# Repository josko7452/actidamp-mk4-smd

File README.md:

# Actidamp Mk. IV - SMD

Low noise RIAA preamplifier with JFET input and active input impedance (to mitigate Johnson noise)

## Schematics

* **Main board** - [pdf link](https://github.com/josko7452/actidamp-mk4-smd/releases/download/2019.11.5/main-pcb.pdf)
* **Power supply** - [pdf link](https://github.com/josko7452/actidamp-mk4-smd/releases/download/2019.11.5/psu-brick.pdf)
* **Front & Back panel** - [pdf link](https://github.com/josko7452/actidamp-mk4-smd/releases/download/2019.11.5/panels.pdf)

## Pictures

## Getting Started

To build this just download Gerbers from release page and hand-off to your favourtie PCB manufacturer.
I have tested it with JLC PCB. But it has no crazy requirements besides the mainboard is 4 layer.

(If you want BOM, download KiCad and generate it from the Schematic, you will likely change parts anyway
dependig on accessibility.. you can shoot me a message and I will send you the Mouser part list from
my order history if you wish)

## Structure

There are 3 KiCad project for each PCB. i.e. *'main-pcb'*, *'panels'* and *'psu-brick'*.
Also there is LTSpice simulation in 'ltspice' subfolder.
Other than that it also cointains KiCad libraries used as submodules (kicad-footprints and kicad-symbols)

## Authors

* **Pavel Dudek** - *Original THT version* - [Amaterske radio 94-06](https://archive.org/stream/Amaterske_radio_1994/94-06#page/n19)
* **Bruno Kremel [me]** - *Modified to SMD and using different JFET*

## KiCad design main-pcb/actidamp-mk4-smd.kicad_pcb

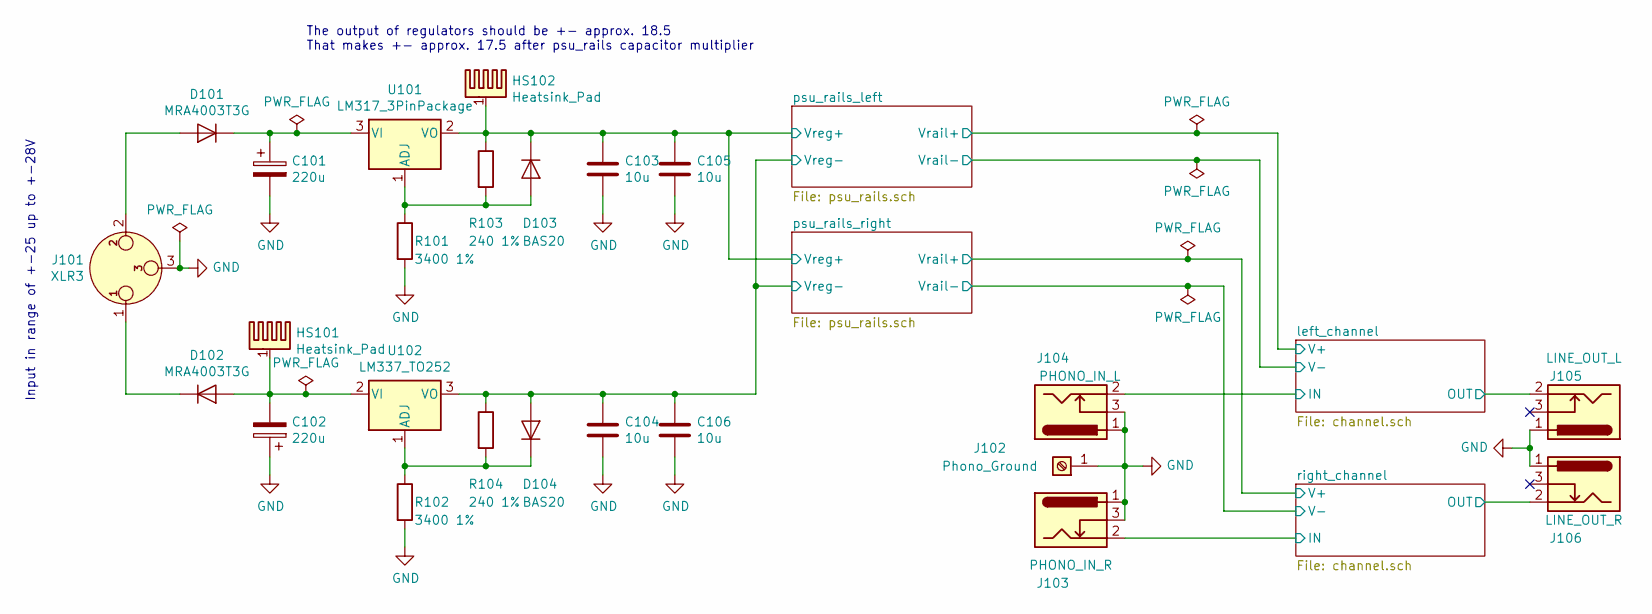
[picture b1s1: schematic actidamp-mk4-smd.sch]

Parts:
C101, C102: 220u; CP_Elec_8x10.5; Part number EEE1EA221UP
C103, C104, C105, C106: 10u; C_1206_3216Metric_Pad1.42x1.75mm_HandSolder; Part number C1206C106K3PACTU
D101, D102: MRA4003T3G; D_SMA; Part number MRA4003T3G
D103, D104: BAS20; D_SOT-23_ANK; Part number BAS20
HS101, HS102: Heatsink_Pad; Heatsink_TO252_573100; Part number FK 244 13 D PAK
J101: XLR3; MiniXLR_TRAPC3M1X; Part number TRAPC3MX
J102: Phono_Ground; SCREW_TERMINAL_SCTM4RA; Part number SCRTM4RA
J103: PHONO_IN_L; RCA_x1_PJRAN1X1U; Part number PJRAN1X1U02AUX
J104: PHONO_IN_R; RCA_x1_PJRAN1X1U; Part number PJRAN1X1U03AUX
J105: LINE_OUT_L; RCA_x1_PJRAN1X1U; Part number PJRAN1X1U02AUX
J106: LINE_OUT_R; RCA_x1_PJRAN1X1U; Part number PJRAN1X1U03AUX
R101, R102: 3400 1%; R_0603_1608Metric_Pad1.05x0.95mm_HandSolder; Part number MCWF06R3401BTL
R103, R104: 240 1%; R_0603_1608Metric_Pad1.05x0.95mm_HandSolder; Part number ERA3AEB241V
U101: LM317_3PinPackage; TO-252-3_TabPin2; Part number LM317MDTX
U102: LM337_TO252; TO-252-3_TabPin2; Part number LM337KVURG3

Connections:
/left_channel/IN: J103.2; also elsewhere on the board
/left_channel/OUT: J105.2; also elsewhere on the board
/psu_rails_left/Vreg+: C103.1, C105.1, D103.1 (K), HS102.1, R103.1, U101.2 (VO); also elsewhere on the board
/psu_rails_left/Vreg-: C104.2, C106.2, D104.2 (A), R104.1, U102.3 (VO); also elsewhere on the board
/right_channel/IN: J104.2; also elsewhere on the board
/right_channel/OUT: J106.2; also elsewhere on the board
GND: C101.2, C102.1, C103.2, C104.1, C105.2, C106.1, J101.3, J102.1, J103.1, J103.3, J104.1, J104.3, J105.1, J106.1, R101.2, R102.2; also elsewhere on the board
unnamed: C101.1, D101.1 (K), U101.3 (VI)
unnamed: C102.2, D102.2 (A), HS101.1, U102.2 (VI)
unnamed: D101.2 (A), J101.2
unnamed: D102.1 (K), J101.1
unnamed: D103.2 (A), R101.1, R103.2, U101.1 (ADJ)
unnamed: D104.1 (K), R102.1, R104.2, U102.1 (ADJ)

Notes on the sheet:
The output of regulators should be +- approx. 18.5 That makes +- approx. 17.5 after psu_rails capacitor multiplier
Input in range of +-25 up to +-28V

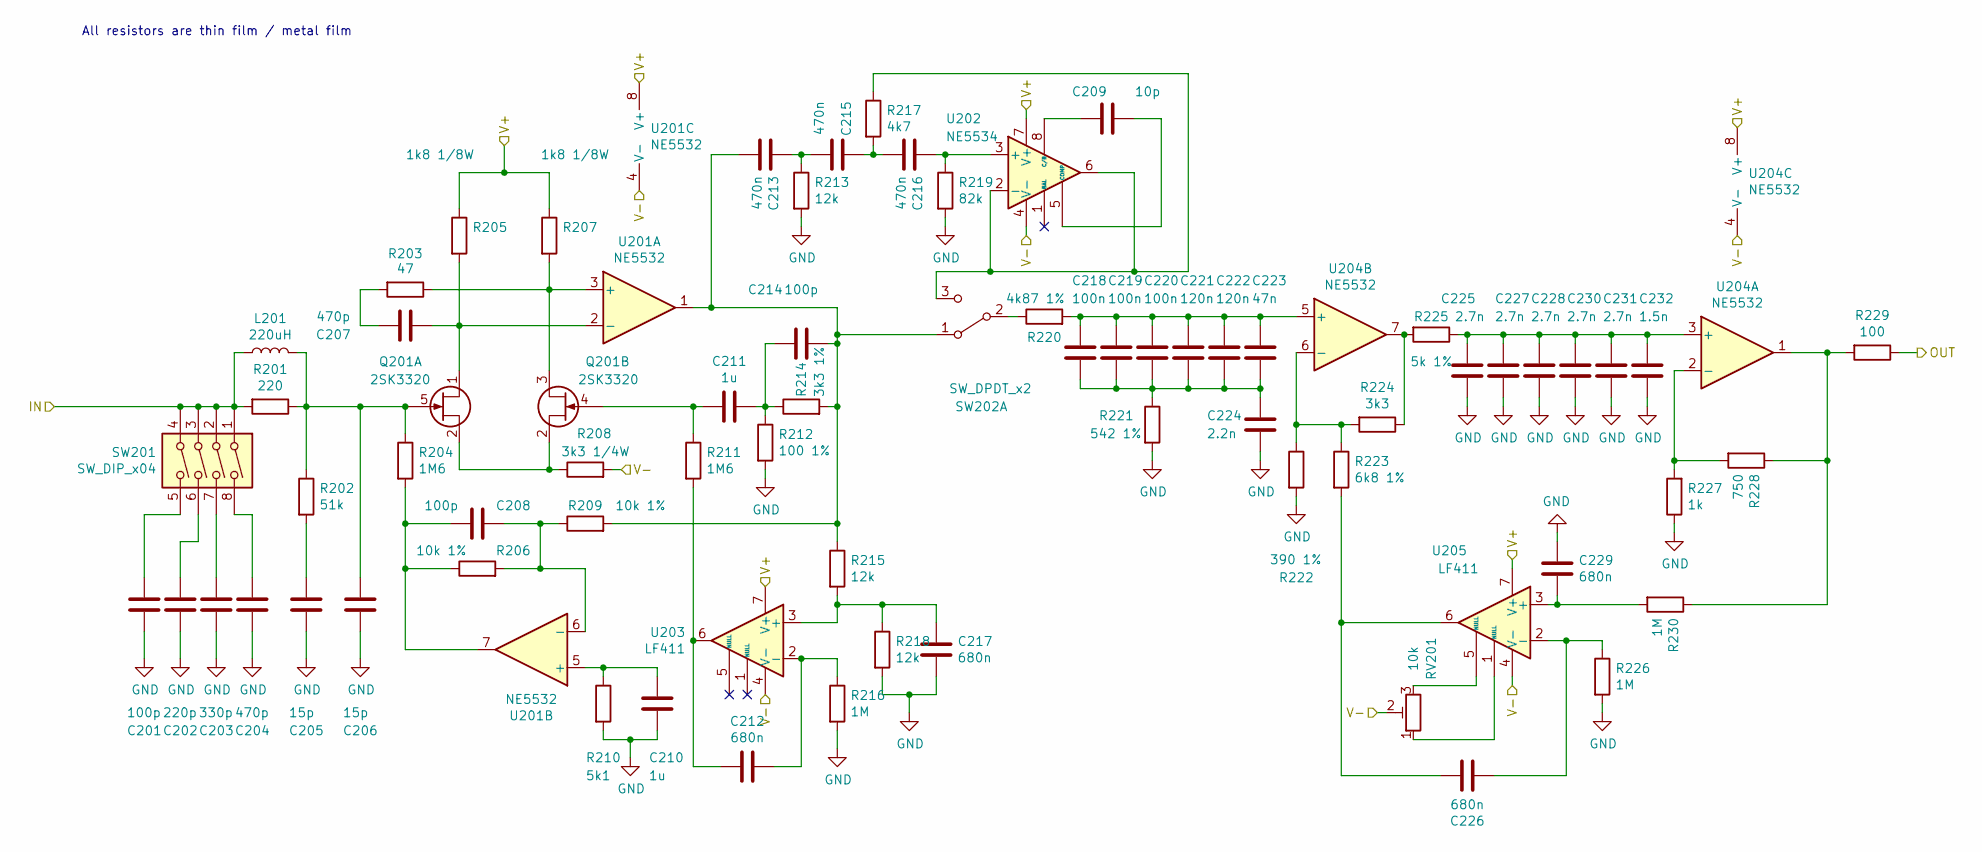
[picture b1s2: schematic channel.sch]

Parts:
C201, C208, C214: 100p; C_0603_1608Metric_Pad1.05x0.95mm_HandSolder; Part number MC0603N101J500CT
C202: 220p; C_0603_1608Metric_Pad1.05x0.95mm_HandSolder; Part number 06035A221JAT2A
C203: 330p; C_0603_1608Metric_Pad1.05x0.95mm_HandSolder; Part number MC0603N331J500CT
C204, C207: 470p; C_0603_1608Metric_Pad1.05x0.95mm_HandSolder; Part number VJ0603A471JXACW1BC
C205, C206: 15p; C_0603_1608Metric_Pad1.05x0.95mm_HandSolder; Part number MC0603N150J500CT
C209: 10p; C_0603_1608Metric_Pad1.05x0.95mm_HandSolder; Part number MC0603N100J500CT
C210, C211: 1u; C_2824_7260Metric_Pad3.20x4.45mm_HandSolder; Part number SMDIC04100TB00KQ00
C212, C217, C226, C229: 680n; C_2824_7260Metric_Pad3.20x4.45mm_HandSolder; Part number SMDIC03680TB00KQ00
C213, C215, C216: 470n; C_2824_7260Metric_Pad3.20x4.45mm_HandSolder; Part number SMDIC03470TB00MQ00
C218, C219, C220: 100n; C_1913_4833Metric_Pad1.3x3.00mm_HandSolder; Part number ECHU1H104GX9
C221, C222: 120n; C_2416_6041Metric_Pad1.5x3.8mm_HandSolder; Part number ECHU1H124GX9
C223: 47n; C_1913_4833Metric_Pad1.3x3.00mm_HandSolder; Part number ECHU1H473GX9
C224: 2.2n; C_0805_2012Metric_Pad1.15x1.1mm_HandSolder; Part number ECHU1H222GX5
C225, C227, C228, C230, C231: 2.7n; C_0805_2012Metric_Pad1.15x1.1mm_HandSolder; Part number ECHU1H272GX5
C232: 1.5n; C_0805_2012Metric_Pad1.15x1.1mm_HandSolder; Part number ECHU1H152GX5
L201: 220uH; L_NLFV32_Pad1.2x2.0mm_HandSolder; Part number NLFV32T-221K-EF
Q201: 2SK3320; SOT-353_SC-70-5_Handsoldering; Part number 2SK3320
R201: 220; R_0603_1608Metric_Pad1.05x0.95mm_HandSolder; Part number ERA3AEB221V
R202: 51k; R_0603_1608Metric_Pad1.05x0.95mm_HandSolder; Part number ERA3AEB513V
R203: 47; R_0603_1608Metric_Pad1.05x0.95mm_HandSolder; Part number RT0603FRE0747RL
R204, R211: 1M6; R_0805_2012Metric_Pad1.15x1.40mm_HandSolder; Part number 1-1614959-2
R205, R207: 1k8 1/8W; R_0805_2012Metric_Pad1.15x1.40mm_HandSolder; Part number RT0805FRE071K8L
R206, R209: 10k 1%; R_0603_1608Metric_Pad1.05x0.95mm_HandSolder; Part number RT0603WRE0710KL
R208: 3k3 1/4W; R_1206_3216Metric_Pad1.42x1.75mm_HandSolder; Part number ERA8ARB332V
R210: 5k1; R_0603_1608Metric_Pad1.05x0.95mm_HandSolder; Part number ERA3AEB512V
R212: 100 1%; R_0603_1608Metric_Pad1.05x0.95mm_HandSolder; Part number RT0603FRE07100RL
R213, R215, R218: 12k; R_0603_1608Metric_Pad1.05x0.95mm_HandSolder; Part number ERA3AEB123V
R214: 3k3 1%; R_0603_1608Metric_Pad1.05x0.95mm_HandSolder; Part number RT0603FRE073K3L
R216, R226, R230: 1M; R_0603_1608Metric_Pad1.05x0.95mm_HandSolder; Part number MCT06030C1004FP500
R217: 4k7; R_0603_1608Metric_Pad1.05x0.95mm_HandSolder; Part number RT0603FRE074K7L
R219: 82k; R_0603_1608Metric_Pad1.05x0.95mm_HandSolder; Part number ERA3AEB823V
R220: 4k87 1%; R_0603_1608Metric_Pad1.05x0.95mm_HandSolder; Part number CPF0603F4K87C1
R221: 542 1%; R_0603_1608Metric_Pad1.05x0.95mm_HandSolder; Part number RN73H1JTTD5420B50
R222: 390 1%; R_0603_1608Metric_Pad1.05x0.95mm_HandSolder; Part number RT0603FRE07390RL
R223: 6k8 1%; R_0603_1608Metric_Pad1.05x0.95mm_HandSolder; Part number RT0603FRE076K8L
R224: 3k3; R_0603_1608Metric_Pad1.05x0.95mm_HandSolder; Part number RT0603FRE073K3L
R225: 5k 1%; R_0603_1608Metric_Pad1.05x0.95mm_HandSolder; Part number RT0603BRE075KL
R227: 1k; R_0603_1608Metric_Pad1.05x0.95mm_HandSolder; Part number RT0603FRE071KL
R228: 750; R_0603_1608Metric_Pad1.05x0.95mm_HandSolder; Part number MCT06030C7500FP500
R229: 100; R_0603_1608Metric_Pad1.05x0.95mm_HandSolder; Part number MCT06030C1000FP500
RV201: 10k; Potentiometer_Vishay_TS53YJ_Vertical; Part number TS53YJ103MR10
SW201: SW_DIP_x04; SW_DIP_SPSTx04_Slide_TE_1571983-5_W6.2mm_P1.27mm; Part number 1571983-5
SW202: SW_DPDT_x2; Wurth_452403012014; Part number 452403012014
U201, U204: NE5532; SOIC-8_3.9x4.9mm_P1.27mm; Part number NE5532DR
U202: NE5534; SOIC-8_3.9x4.9mm_P1.27mm; Part number NE5534ADG
U203, U205: LF411; SOIC-8_3.9x4.9mm_P1.27mm; Part number LF411CD

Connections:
/left_channel/IN: L201.1, R201.2, SW201.1, SW201.2, SW201.3, SW201.4; also elsewhere on the board
/left_channel/OUT: R229.1; also elsewhere on the board
/left_channel/V+: R205.1, R207.1, U201.8 (V+), U202.7 (V+), U203.7 (V+), U204.8 (V+), U205.7 (V+); also elsewhere on the board
/left_channel/V-: R208.2, RV201.2, U201.4 (V-), U202.4 (V-), U203.4 (V-), U204.4 (V-), U205.4 (V-); also elsewhere on the board
GND: C201.2, C202.2, C203.2, C204.2, C205.2, C206.2, C210.2, C217.2, C224.2, C225.2, C227.2, C228.2, C229.1, C230.2, C231.2, C232.2, R210.2, R212.2, R213.2, R216.2, R218.2, R219.2, R221.2, R222.2, R226.2, R227.1; also elsewhere on the board
unnamed: C201.1, SW201.5
unnamed: C202.1, SW201.6
unnamed: C203.1, SW201.7
unnamed: C204.1, SW201.8
unnamed: C205.1, R202.2
unnamed: C206.1, L201.2, Q201.5 (G), R201.1, R202.1, R204.1
unnamed: C207.1, Q201.1 (D), R205.2, U201.2 (-)
unnamed: C207.2, R203.2
unnamed: C208.1, R206.2, R209.1, U201.6 (-)
unnamed: C208.2, R204.2, R206.1, U201.7
unnamed: C209.1, U202.5 (COMP)
unnamed: C209.2, U202.8 (C/B)
unnamed: C210.1, R210.1, U201.5 (+)
unnamed: C211.1, C214.2, R212.1, R214.1
unnamed: C211.2, Q201.4 (G), R211.1
unnamed: C212.1, R216.1, U203.2 (-)
unnamed: C212.2, R211.2, U203.6
unnamed: C213.1, C215.2, R213.1
unnamed: C213.2, C214.1, R209.2, R214.2, R215.1, SW202.1 (A), U201.1
unnamed: C215.1, C216.2, R217.2
unnamed: C216.1, R219.1, U202.3 (+)
unnamed: C217.1, R215.2, R218.1, U203.3 (+)
unnamed: C218.1, C219.1, C220.1, C221.1, C222.1, C223.1, R220.2, U204.5 (+)
unnamed: C218.2, C219.2, C220.2, C221.2, C222.2, C223.2, C224.1, R221.1
unnamed: C225.1, C227.1, C228.1, C230.1, C231.1, C232.1, R225.1, U204.3 (+)
unnamed: C226.1, R223.2, U205.6
unnamed: C226.2, R226.1, U205.2 (-)
unnamed: C229.2, R230.2, U205.3 (+)
unnamed 59: SW202.4 (A); also elsewhere on the board
unnamed: Q201.2 (S), R208.1
unnamed: Q201.3 (D), R203.1, R207.2, U201.3 (+)
unnamed: R217.1, SW202.3 (C), U202.2 (-), U202.6
unnamed: R220.1, SW202.2 (B)
unnamed: R222.1, R223.1, R224.2, U204.6 (-)
unnamed: R224.1, R225.2, U204.7
unnamed: R227.2, R228.2, U204.2 (-)
unnamed: R228.1, R229.2, R230.1, U204.1
unnamed 97: SW202.6 (C); also elsewhere on the board
unnamed 98: SW202.5 (B); also elsewhere on the board
unnamed: RV201.1, U205.1 (NULL)
unnamed: RV201.3, U205.5 (NULL)

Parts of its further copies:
C301, C308, C314: 100p; C_0603_1608Metric_Pad1.05x0.95mm_HandSolder; Part number MC0603N101J500CT
C302: 220p; C_0603_1608Metric_Pad1.05x0.95mm_HandSolder; Part number 06035A221JAT2A
C303: 330p; C_0603_1608Metric_Pad1.05x0.95mm_HandSolder; Part number MC0603N331J500CT
C304, C307: 470p; C_0603_1608Metric_Pad1.05x0.95mm_HandSolder; Part number VJ0603A471JXACW1BC
C305, C306: 15p; C_0603_1608Metric_Pad1.05x0.95mm_HandSolder; Part number MC0603N150J500CT
C309: 10p; C_0603_1608Metric_Pad1.05x0.95mm_HandSolder; Part number MC0603N100J500CT
C310, C311: 1u; C_2824_7260Metric_Pad3.20x4.45mm_HandSolder; Part number SMDIC04100TB00KQ00
C312, C317, C326, C329: 680n; C_2824_7260Metric_Pad3.20x4.45mm_HandSolder; Part number SMDIC03680TB00KQ00
C313, C315, C316: 470n; C_2824_7260Metric_Pad3.20x4.45mm_HandSolder; Part number SMDIC03470TB00MQ00
C318, C319, C320: 100n; C_1913_4833Metric_Pad1.3x3.00mm_HandSolder; Part number ECHU1H104GX9
C321, C322: 120n; C_2416_6041Metric_Pad1.5x3.8mm_HandSolder; Part number ECHU1H124GX9
C323: 47n; C_1913_4833Metric_Pad1.3x3.00mm_HandSolder; Part number ECHU1H473GX9
C325, C327, C328, C330, C331: 2.7n; C_0805_2012Metric_Pad1.15x1.1mm_HandSolder; Part number ECHU1H272GX5
C332: 1.5n; C_0805_2012Metric_Pad1.15x1.1mm_HandSolder; Part number ECHU1H152GX5
L301: 220uH; L_NLFV32_Pad1.2x2.0mm_HandSolder; Part number NLFV32T-221K-EF
Q301: 2SK3320; SOT-353_SC-70-5_Handsoldering; Part number 2SK3320
R301: 220; R_0603_1608Metric_Pad1.05x0.95mm_HandSolder; Part number ERA3AEB221V
R302: 51k; R_0603_1608Metric_Pad1.05x0.95mm_HandSolder; Part number ERA3AEB513V
R303: 47; R_0603_1608Metric_Pad1.05x0.95mm_HandSolder; Part number RT0603FRE0747RL
R304, R311: 1M6; R_0805_2012Metric_Pad1.15x1.40mm_HandSolder; Part number 1-1614959-2
R305, R307: 1k8 1/8W; R_0805_2012Metric_Pad1.15x1.40mm_HandSolder; Part number RT0805FRE071K8L
R306, R309: 10k 1%; R_0603_1608Metric_Pad1.05x0.95mm_HandSolder; Part number RT0603WRE0710KL
R308: 3k3 1/4W; R_1206_3216Metric_Pad1.42x1.75mm_HandSolder; Part number ERA8ARB332V
R310: 5k1; R_0603_1608Metric_Pad1.05x0.95mm_HandSolder; Part number ERA3AEB512V
R312: 100 1%; R_0603_1608Metric_Pad1.05x0.95mm_HandSolder; Part number RT0603FRE07100RL
R313, R315, R318: 12k; R_0603_1608Metric_Pad1.05x0.95mm_HandSolder; Part number ERA3AEB123V
R314: 3k3 1%; R_0603_1608Metric_Pad1.05x0.95mm_HandSolder; Part number RT0603FRE073K3L
R316, R326, R330: 1M; R_0603_1608Metric_Pad1.05x0.95mm_HandSolder; Part number MCT06030C1004FP500
R317: 4k7; R_0603_1608Metric_Pad1.05x0.95mm_HandSolder; Part number RT0603FRE074K7L
R319: 82k; R_0603_1608Metric_Pad1.05x0.95mm_HandSolder; Part number ERA3AEB823V
R320: 4k87 1%; R_0603_1608Metric_Pad1.05x0.95mm_HandSolder; Part number CPF0603F4K87C1
R321: 542 1%; R_0603_1608Metric_Pad1.05x0.95mm_HandSolder; Part number RN73H1JTTD5420B50
R322: 390 1%; R_0603_1608Metric_Pad1.05x0.95mm_HandSolder; Part number RT0603FRE07390RL
R323: 6k8 1%; R_0603_1608Metric_Pad1.05x0.95mm_HandSolder; Part number RT0603FRE076K8L
R324: 3k3; R_0603_1608Metric_Pad1.05x0.95mm_HandSolder; Part number RT0603FRE073K3L
R325: 5k 1%; R_0603_1608Metric_Pad1.05x0.95mm_HandSolder; Part number RT0603BRE075KL
R327: 1k; R_0603_1608Metric_Pad1.05x0.95mm_HandSolder; Part number RT0603FRE071KL
R328: 750; R_0603_1608Metric_Pad1.05x0.95mm_HandSolder; Part number MCT06030C7500FP500
R329: 100; R_0603_1608Metric_Pad1.05x0.95mm_HandSolder; Part number MCT06030C1000FP500
RV301: 10k; Potentiometer_Vishay_TS53YJ_Vertical; Part number TS53YJ103MR10
SW301: SW_DIP_x04; SW_DIP_SPSTx04_Slide_TE_1571983-5_W6.2mm_P1.27mm; Part number 1571983-5
U301, U304: NE5532; SOIC-8_3.9x4.9mm_P1.27mm; Part number NE5532DR
U302: NE5534; SOIC-8_3.9x4.9mm_P1.27mm; Part number NE5534ADG
U303, U305: LF411; SOIC-8_3.9x4.9mm_P1.27mm; Part number LF411CD

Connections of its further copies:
/right_channel/IN: L301.1, R301.2, SW301.1, SW301.2, SW301.3, SW301.4; also elsewhere on the board
/right_channel/OUT: R329.1; also elsewhere on the board
/right_channel/V+: R305.1, R307.1, U301.8 (V+), U302.7 (V+), U303.7 (V+), U304.8 (V+), U305.7 (V+); also elsewhere on the board
/right_channel/V-: R308.2, RV301.2, U301.4 (V-), U302.4 (V-), U303.4 (V-), U304.4 (V-), U305.4 (V-); also elsewhere on the board
GND: C301.2, C302.2, C303.2, C304.2, C305.2, C306.2, C310.2, C317.2, C325.2, C327.2, C328.2, C329.1, C330.2, C331.2, C332.2, R310.2, R312.2, R313.2, R316.2, R318.2, R319.2, R321.2, R322.2, R326.2, R327.1; also elsewhere on the board
unnamed: C301.1, SW301.5
unnamed: C302.1, SW301.6
unnamed: C303.1, SW301.7
unnamed: C304.1, SW301.8
unnamed: C305.1, R302.2
unnamed: C306.1, L301.2, Q301.5 (G), R301.1, R302.1, R304.1
unnamed: C307.1, Q301.1 (D), R305.2, U301.2 (-)
unnamed: C307.2, R303.2
unnamed: C308.1, R306.2, R309.1, U301.6 (-)
unnamed: C308.2, R304.2, R306.1, U301.7
unnamed: C309.1, U302.5 (COMP)
unnamed: C309.2, U302.8 (C/B)
unnamed: C310.1, R310.1, U301.5 (+)
unnamed: C311.1, C314.2, R312.1, R314.1
unnamed: C311.2, Q301.4 (G), R311.1
unnamed: C312.1, R316.1, U303.2 (-)
unnamed: C312.2, R311.2, U303.6
unnamed: C313.1, C315.2, R313.1
unnamed 59: C313.2, C314.1, R309.2, R314.2, R315.1, U301.1; also elsewhere on the board
unnamed: C315.1, C316.2, R317.2
unnamed: C316.1, R319.1, U302.3 (+)
unnamed: C317.1, R315.2, R318.1, U303.3 (+)
unnamed: C318.1, C319.1, C320.1, C321.1, C322.1, C323.1, R320.2, U304.5 (+)
unnamed 64: C318.2, C319.2, C320.2, C321.2, C322.2, C323.2, R321.1; also elsewhere on the board
unnamed: C325.1, C327.1, C328.1, C330.1, C331.1, C332.1, R325.1, U304.3 (+)
unnamed: C326.1, R323.2, U305.6
unnamed: C326.2, R326.1, U305.2 (-)
unnamed: C329.2, R330.2, U305.3 (+)
unnamed: Q301.2 (S), R308.1
unnamed: Q301.3 (D), R303.1, R307.2, U301.3 (+)
unnamed 97: R317.1, U302.2 (-), U302.6; also elsewhere on the board
unnamed 98: R320.1; also elsewhere on the board
unnamed: R322.1, R323.1, R324.2, U304.6 (-)
unnamed: R324.1, R325.2, U304.7
unnamed: R327.2, R328.2, U304.2 (-)
unnamed: R328.1, R329.2, R330.1, U304.1
unnamed: RV301.1, U305.1 (NULL)
unnamed: RV301.3, U305.5 (NULL)

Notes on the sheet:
All resistors are thin film / metal film

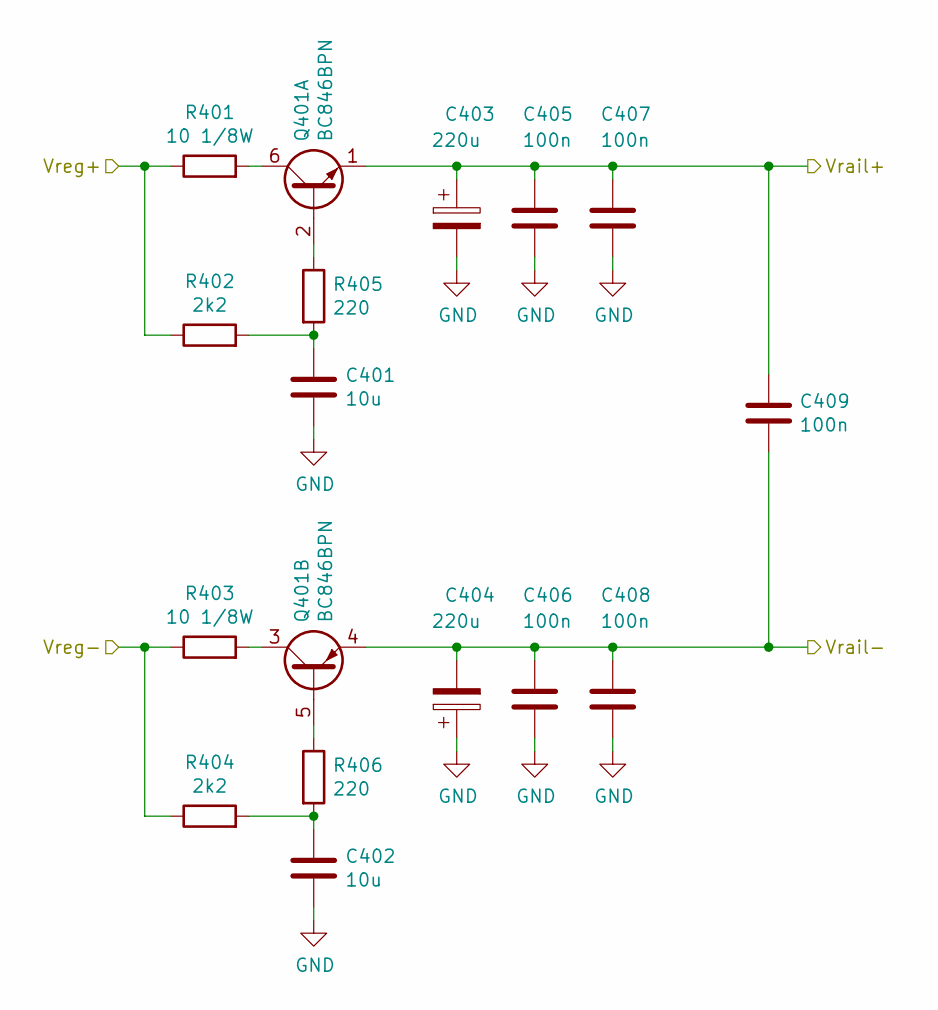
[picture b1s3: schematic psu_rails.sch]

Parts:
C401, C402: 10u; C_1206_3216Metric_Pad1.42x1.75mm_HandSolder; Part number C1206C106K3PACTU
C403, C404: 220u; CP_Elec_8x10.5; Part number EEE1EA221UP
C405, C406, C407, C408, C409: 100n; C_0603_1608Metric_Pad1.05x0.95mm_HandSolder; Part number VJ0603Y104KXACW1BC
Q401: BC846BPN; SOT-363_SC-70-6; Part number BC846BPN
R401, R403: 10 1/8W; R_0805_2012Metric_Pad1.15x1.40mm_HandSolder; Part number MCWF08U10RBTL
R402, R404: 2k2; R_0603_1608Metric_Pad1.05x0.95mm_HandSolder; Part number RT0603FRE072K2L
R405, R406: 220; R_0603_1608Metric_Pad1.05x0.95mm_HandSolder; Part number ERA3AEB221V

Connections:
/left_channel/V+: C403.1, C405.1, C407.1, C409.1, Q401.1 (E1); also elsewhere on the board
/left_channel/V-: C404.2, C406.1, C408.1, C409.2, Q401.4 (E2); also elsewhere on the board
/psu_rails_left/Vreg+: R401.1, R402.1; also elsewhere on the board
/psu_rails_left/Vreg-: R403.1, R404.1; also elsewhere on the board
GND: C401.2, C402.1, C403.2, C404.1, C405.2, C406.2, C407.2, C408.2; also elsewhere on the board
unnamed: C401.1, R402.2, R405.2
unnamed: C402.2, R404.2, R406.2
unnamed: Q401.2 (B1), R405.1
unnamed: Q401.3 (C2), R403.2
unnamed: Q401.5 (B2), R406.1
unnamed: Q401.6 (C1), R401.2

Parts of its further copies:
C501, C502: 10u; C_1206_3216Metric_Pad1.42x1.75mm_HandSolder; Part number C1206C106K3PACTU
C503, C504: 220u; CP_Elec_8x10.5; Part number EEE1EA221UP
C505, C506, C507, C508, C509: 100n; C_0603_1608Metric_Pad1.05x0.95mm_HandSolder; Part number VJ0603Y104KXACW1BC
Q501: BC846BPN; SOT-363_SC-70-6; Part number BC846BPN
R501, R503: 10 1/8W; R_0805_2012Metric_Pad1.15x1.40mm_HandSolder; Part number MCWF08U10RBTL
R502, R504: 2k2; R_0603_1608Metric_Pad1.05x0.95mm_HandSolder; Part number RT0603FRE072K2L
R505, R506: 220; R_0603_1608Metric_Pad1.05x0.95mm_HandSolder; Part number ERA3AEB221V

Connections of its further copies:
/psu_rails_left/Vreg+: R501.1, R502.1; also elsewhere on the board
/psu_rails_left/Vreg-: R503.1, R504.1; also elsewhere on the board
/right_channel/V+: C503.1, C505.1, C507.1, C509.1, Q501.1 (E1); also elsewhere on the board
/right_channel/V-: C504.2, C506.1, C508.1, C509.2, Q501.4 (E2); also elsewhere on the board
GND: C501.2, C502.1, C503.2, C504.1, C505.2, C506.2, C507.2, C508.2; also elsewhere on the board
unnamed: C501.1, R502.2, R505.2
unnamed: C502.2, R504.2, R506.2
unnamed: Q501.2 (B1), R505.1
unnamed: Q501.3 (C2), R503.2
unnamed: Q501.5 (B2), R506.1
unnamed: Q501.6 (C1), R501.2

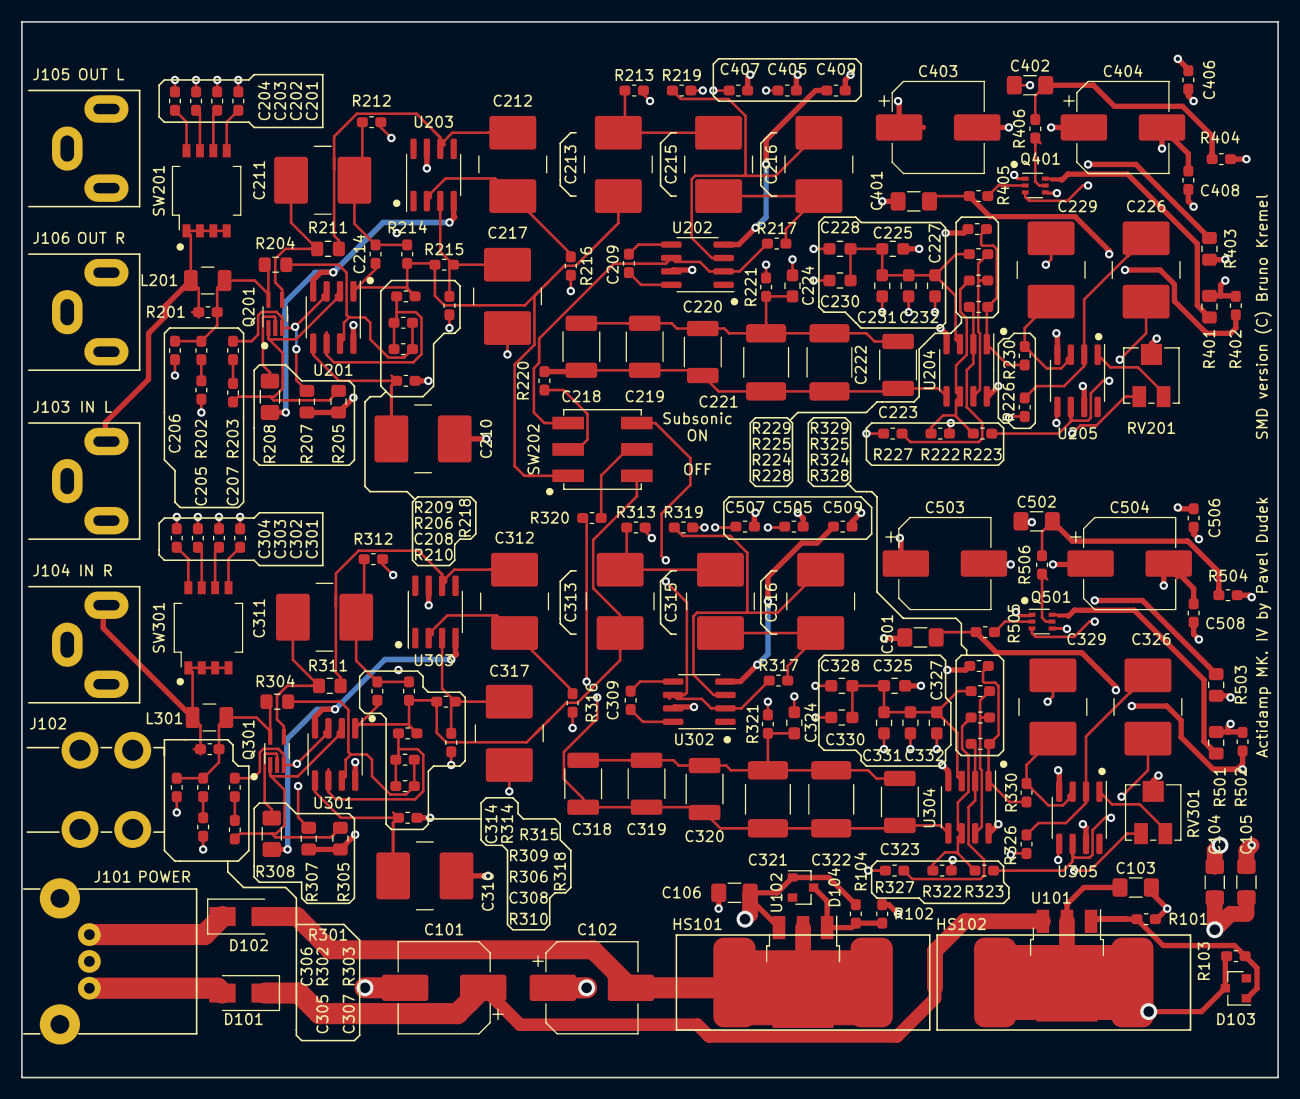
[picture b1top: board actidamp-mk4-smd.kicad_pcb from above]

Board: 4 copper layers, 119.0 x 100.0 mm, 199 parts (0 on the bottom side), 105 nets.

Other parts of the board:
C324: 220p; C_0805_2012Metric_Pad1.15x1.1mm_HandSolder

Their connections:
GND: C324.2; also elsewhere on the board
unnamed 64: C324.1; also elsewhere on the board

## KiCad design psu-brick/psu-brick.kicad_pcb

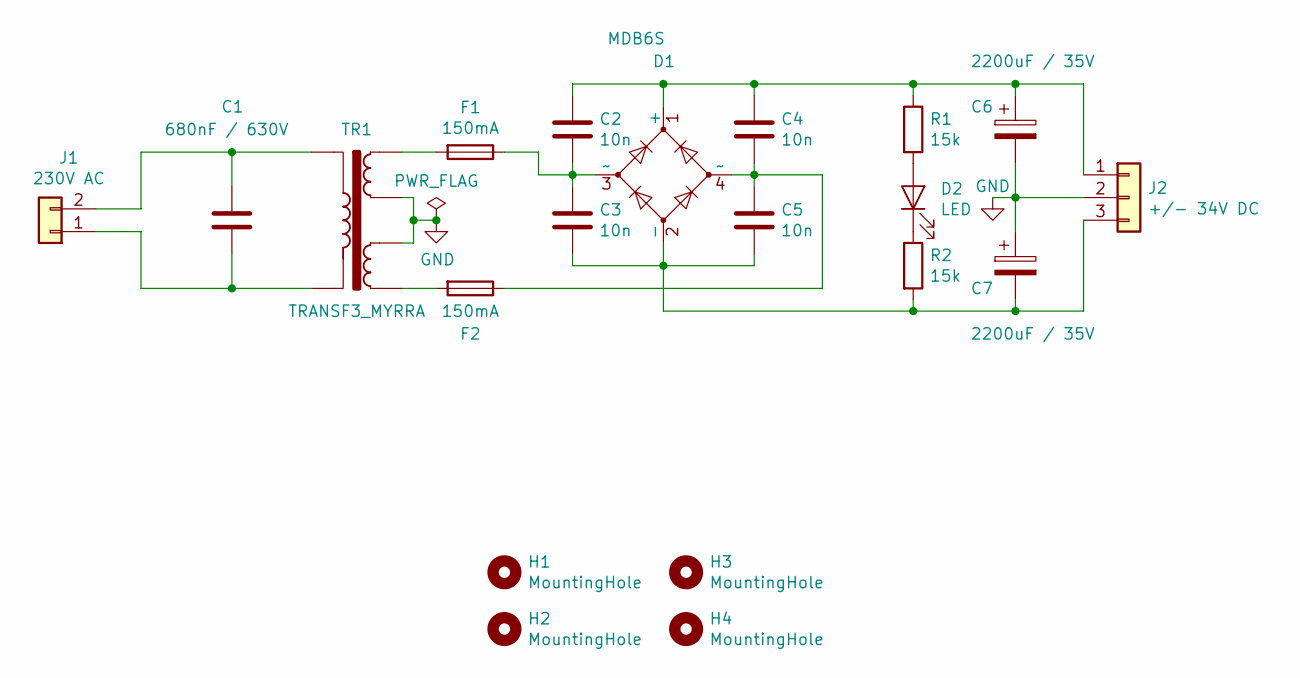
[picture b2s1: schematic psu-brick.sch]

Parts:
C1: 680nF / 630V; C_Rect_L7.2mm_W7.2mm_P5.00mm_FKS2_FKP2_MKS2_MKP2; Part number MKP2J016801C00KSSD
C2, C3, C4, C5: 10n; C_0805_2012Metric_Pad1.15x1.40mm_HandSolder
C6, C7: 2200uF / 35V; CP_Radial_D16.0mm_P7.50mm
D1: MDB6S
D2: LED; LED_D5.0mm; Part number LTL2R3KRD-EM
F1, F2: 150mA; Fuseholder_Cylinder-5x20mm_Schurter_0031_8201_Horizontal_Op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; Part number 0031.8201
H1, H2, H3, H4: MountingHole; MountingHole_3.5mm
J1: 230V AC; AC_entry_770W-X2; Part number 770W-X2/10
J2: +/- 34V DC; TerminalBlock_TE_282834-3_1x03_P2.54mm_Horizontal
R1, R2: 15k; R_1206_3216Metric_Pad1.42x1.75mm_HandSolder
TR1: TRANSF3_MYRRA; Transformer_Myrra_44x

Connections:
GND: C6.2, C7.1, J2.2, TR1.7, TR1.9
unnamed: C1.1, J1.2, TR1.1
unnamed: C1.2, J1.1, TR1.5
unnamed: C2.1, C4.1, C6.1, D1.1 (+), J2.1, R1.1
unnamed: C2.2, C3.1, D1.3 (~~), F1.1
unnamed: C3.2, C5.2, C7.2, D1.2 (-), J2.3, R2.2
unnamed: C4.2, C5.1, D1.4 (~~), F2.1
unnamed: D2.1 (K), R2.1
unnamed: D2.2 (A), R1.2
unnamed: F1.2, TR1.6
unnamed: F2.2, TR1.10

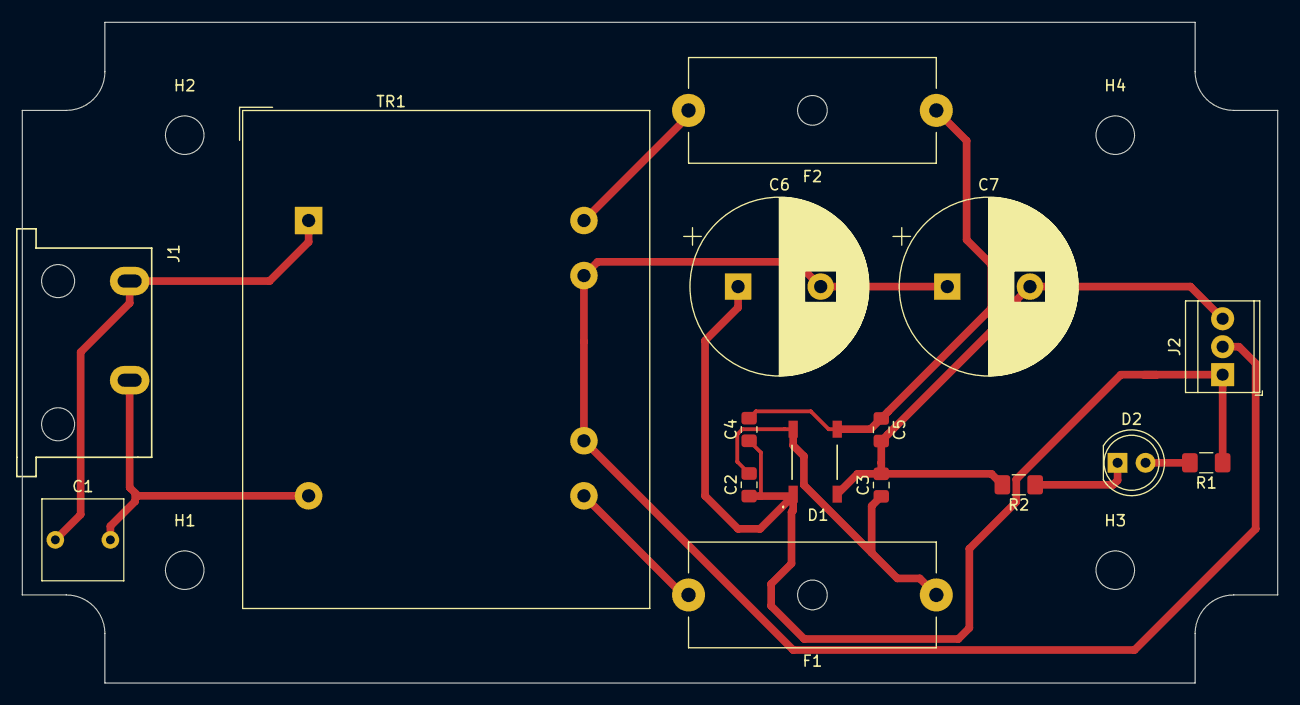
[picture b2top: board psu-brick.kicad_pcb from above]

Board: 2 copper layers, 114.0 x 60.0 mm, 20 parts (0 on the bottom side), 11 nets.

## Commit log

2019-02-21 Add initial files
2019-02-21 Add initial schematics WIP
2019-02-21 Update symbols
2019-02-21 Move stuff to hierarchy
2019-02-21 Add actidamp lib
2019-02-21 Update misc files
2019-02-21 Capture of original actidamp iv
2019-08-26 Assign capacitors, redo hierarchy
2019-08-29 All schematics drafted
2019-09-01 Update symbol and footprint library
2019-09-01 Finalise schematics with power supplies and successful ERC
2019-09-01 Finalise BOM
2019-09-02 WIP: Assign footprints
2019-09-03 WIP: Assigning footprints
2019-09-03 Fix ERC errors
2019-09-04 Finish footprints
2019-09-05 Routing.. routing.. routing
2019-09-06 All components placed on board
2019-09-09 More routing
2019-09-10 All routed
2019-10-16 Finish silkscreen
2019-10-21 Just layer visibility..
2019-10-21 Split to multiple kicad projects
2019-10-21 Fix library paths after move
2019-10-21 Add PSU brick
2019-10-30 Add components for PSU brick
2019-10-30 Add components for FP
2019-10-30 Fix pad for heatsing (it was too small)
2019-10-30 Fix wrong sizes of the SMD switch
2019-10-30 Finish PSU brick
2019-10-30 Add panels
2019-10-30 Add Transformer to lib
2019-10-30 Add fp-info-cache to gitignore
2019-10-30 Maek board 100mm wide, fix track too close to the edge
2019-10-30 Add 1.2mm track width
2019-10-30 Do not store fp-info-cache
2019-10-30 After print v5
2019-10-30 Mage gitignore more ignorant
2019-10-30 Some minor modifications
2019-11-04 Add custom frontpanel/backpanel footprints
2019-11-04 Update panels with custom footprints
2019-11-04 Add graphic custom symbol
2019-11-04 Add all shapes for FB/BP to mask layer as well
2019-11-04 Use only mask layer for FB/BP
2019-11-04 Add gerbers folders to gitignore
2019-11-04 Fix unconnected wire
2019-11-04 Generate gerbers
2019-11-04 Update PSU brich cache
2019-11-04 Add custom JLC number to bottom silkscreen
2019-11-05 Fix stub width for JLCPcb
2019-12-02 Add LTSpice simulation files
2019-12-02 Add pdfs and ltspice output to gitignore
2019-12-02 Add images
2019-12-02 Add thumbnails
2019-12-02 Add md
2019-12-02 Add project structure
